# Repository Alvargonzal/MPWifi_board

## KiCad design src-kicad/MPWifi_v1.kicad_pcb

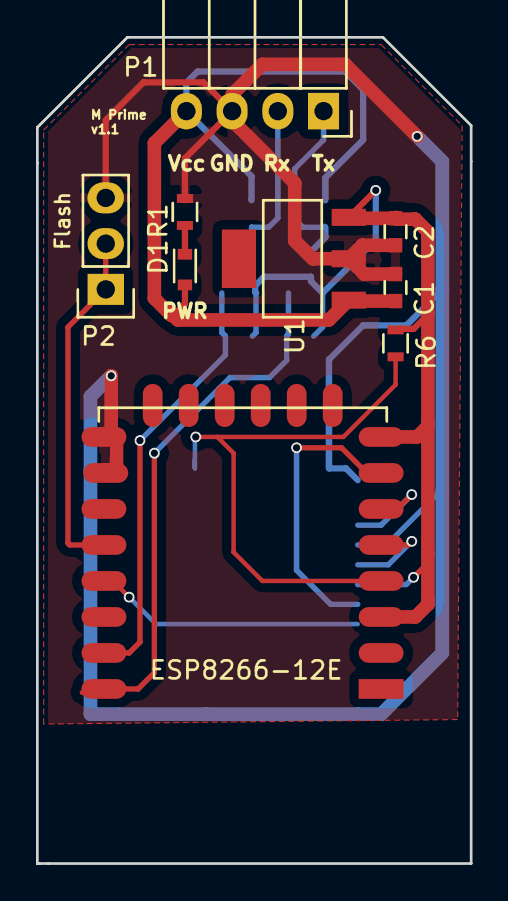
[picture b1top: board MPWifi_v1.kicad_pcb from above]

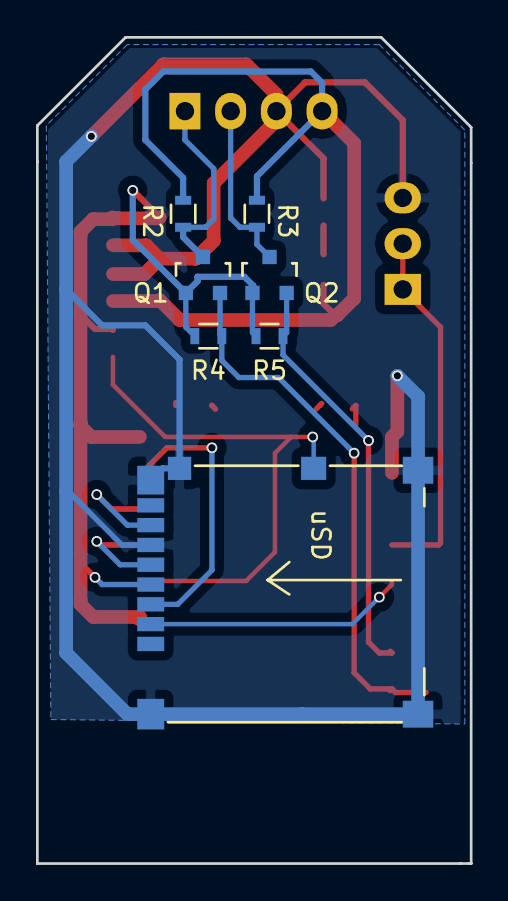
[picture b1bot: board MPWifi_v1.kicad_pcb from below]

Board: 2 copper layers, 24.1 x 45.9 mm, 16 parts (7 on the bottom side), 14 nets.

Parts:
C1, C2: 1uF; C_0603
D1: LED; D_0603
M1: ESP8266-12E
P1: CONN_01X04; Socket_Strip_Angled_1x04
P2: Flash; Pin_Header_Straight_1x03
Q1, Q2: BSS138; SOT-23
R1: 140; R_0603
R2, R3, R4, R5, R6: 10k; R_0603
U1: MCP1703T-3302E/CB; SOT-223-3
uSD: Micro_SD_Card; MicroSD-slot

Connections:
+3V3: C2.1, M1.3, M1.8, Q1.1, Q2.1, R4.2, R5.2, R6.1, U1.3, uSD.4
/CS: M1.13, uSD.2
/DETECT_SWITCH: M1.4, R6.2, uSD.11
/MISO: M1.6, uSD.7
/MOSI: M1.7, uSD.3
/RX: P1.2, Q2.3, R3.2
/SCLK: M1.5, uSD.5
/TX: P1.1, Q1.3, R2.2
GND: C1.2, C2.2, M1.9, M1.10, P1.3, P2.3, R1.2, U1.2, uSD.6, uSD.9, uSD.10
unnamed: D1.1, R1.1
unnamed: M1.12, P2.1, P2.2
unnamed: M1.15, Q2.2, R5.1
unnamed: M1.16, Q1.2, R4.1
VCC: C1.1, D1.2, P1.4, R2.1, R3.1, U1.1

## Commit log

2016-11-15 Schema
2016-11-18 Netlist
2016-11-21 Board v1.0 and BOM
2016-11-21 BOM update
2016-11-22 v1.0 PCB
2016-11-23 BOM reference update
2017-01-03 Update before change branch
2017-01-03 microSD footprint & retrack
2017-01-03 Manufacturing files

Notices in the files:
src-kicad/MPWifi_v1.kicad_pcb:
License:
